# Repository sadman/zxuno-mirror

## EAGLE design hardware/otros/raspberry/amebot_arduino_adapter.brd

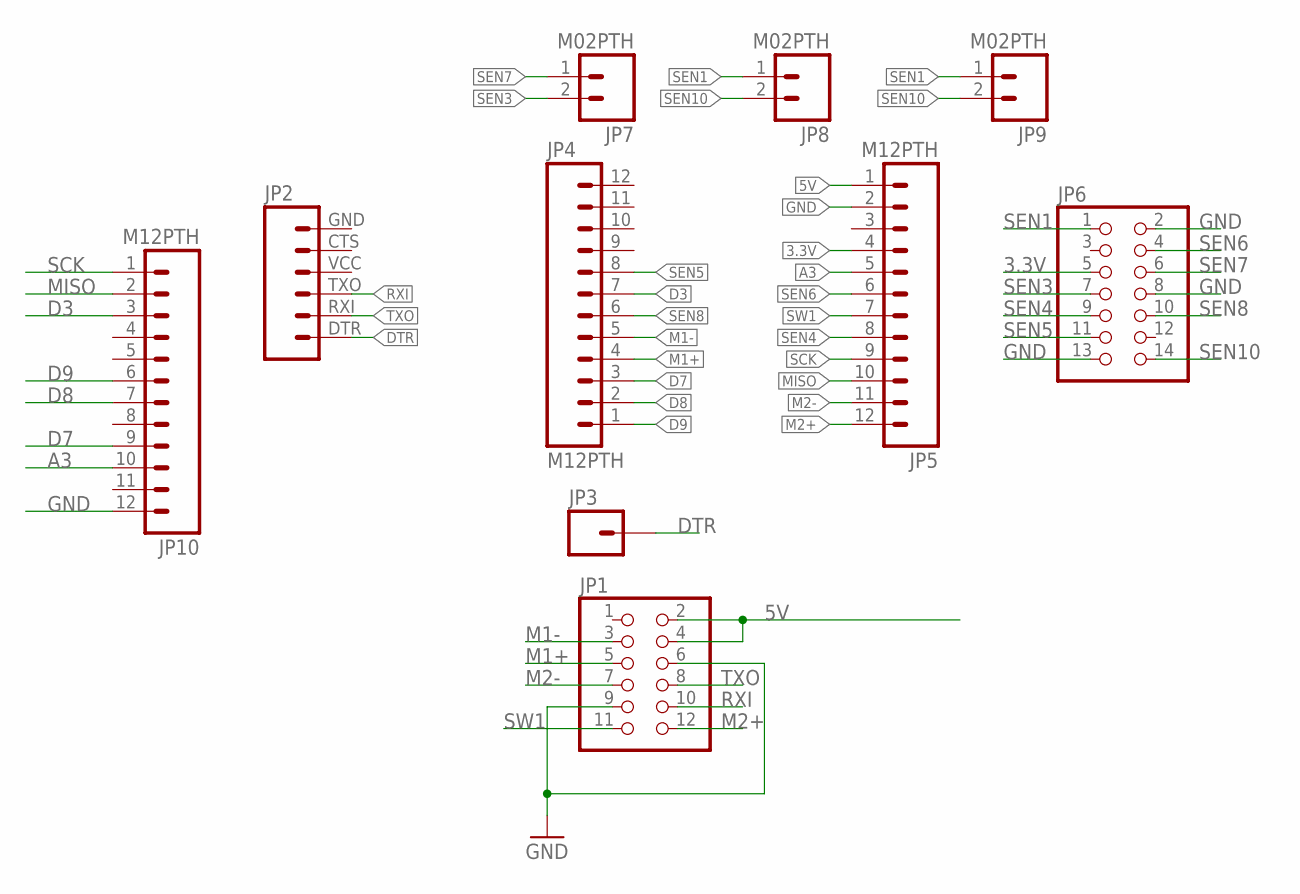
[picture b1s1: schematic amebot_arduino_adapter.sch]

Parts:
JP1: PINHD-2X6; 2X06
JP2: M06SIP; 1X06
JP3: M01PTH_LONGPAD; 1X01_LONGPAD
JP4, JP5, JP10: M12PTH; 1X12
JP6: PINHD-2X7; 2X07
JP7, JP8, JP9: M02PTH; 1X02

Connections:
3.3V: JP5.4, JP6.5
5V: JP1.2, JP1.4, JP5.1
A3: JP5.5, JP10.10
D3: JP4.7, JP10.3
D7: JP4.3, JP10.9
D8: JP4.2, JP10.7
D9: JP4.1, JP10.6
DTR: JP2.DTR (1), JP3.1
GND: JP1.6, JP1.9, JP5.2, JP6.2, JP6.8, JP6.13, JP10.12
M1+: JP1.5, JP4.4
M1-: JP1.3, JP4.5
M2+: JP1.12, JP5.12
M2-: JP1.7, JP5.11
MISO: JP5.10, JP10.2
RXI: JP1.10, JP2.TXO (3)
SCK: JP5.9, JP10.1
SEN1: JP6.1, JP8.1, JP9.1
SEN3: JP6.7, JP7.2
SEN4: JP5.8, JP6.9
SEN5: JP4.8, JP6.11
SEN6: JP5.6, JP6.4
SEN7: JP6.6, JP7.1
SEN8: JP4.6, JP6.10
SEN10: JP6.14, JP8.2, JP9.2
SW1: JP1.11, JP5.7
TXO: JP1.8, JP2.RXI (2)

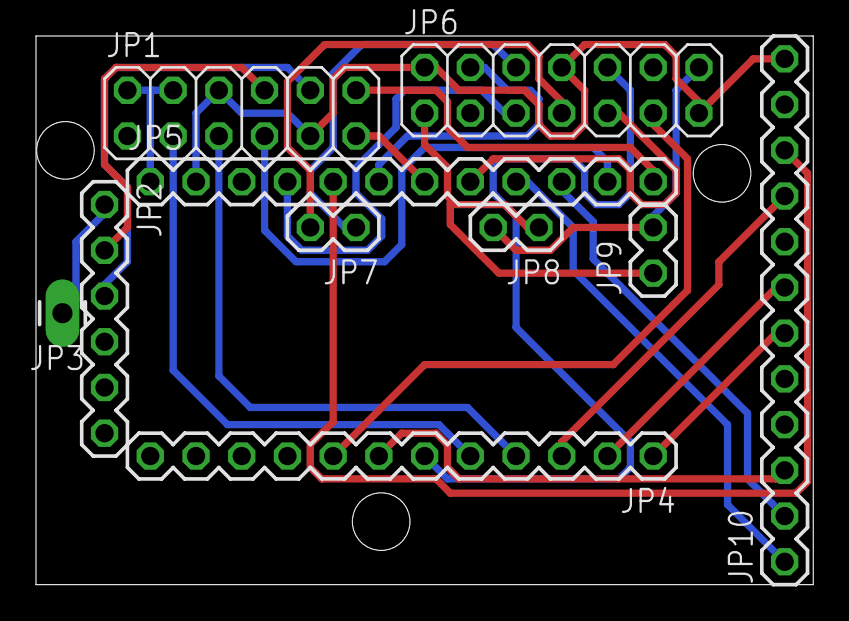
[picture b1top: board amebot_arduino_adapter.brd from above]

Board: 2 copper layers, 43.2 x 30.5 mm, 10 parts (0 on the bottom side), 26 nets.

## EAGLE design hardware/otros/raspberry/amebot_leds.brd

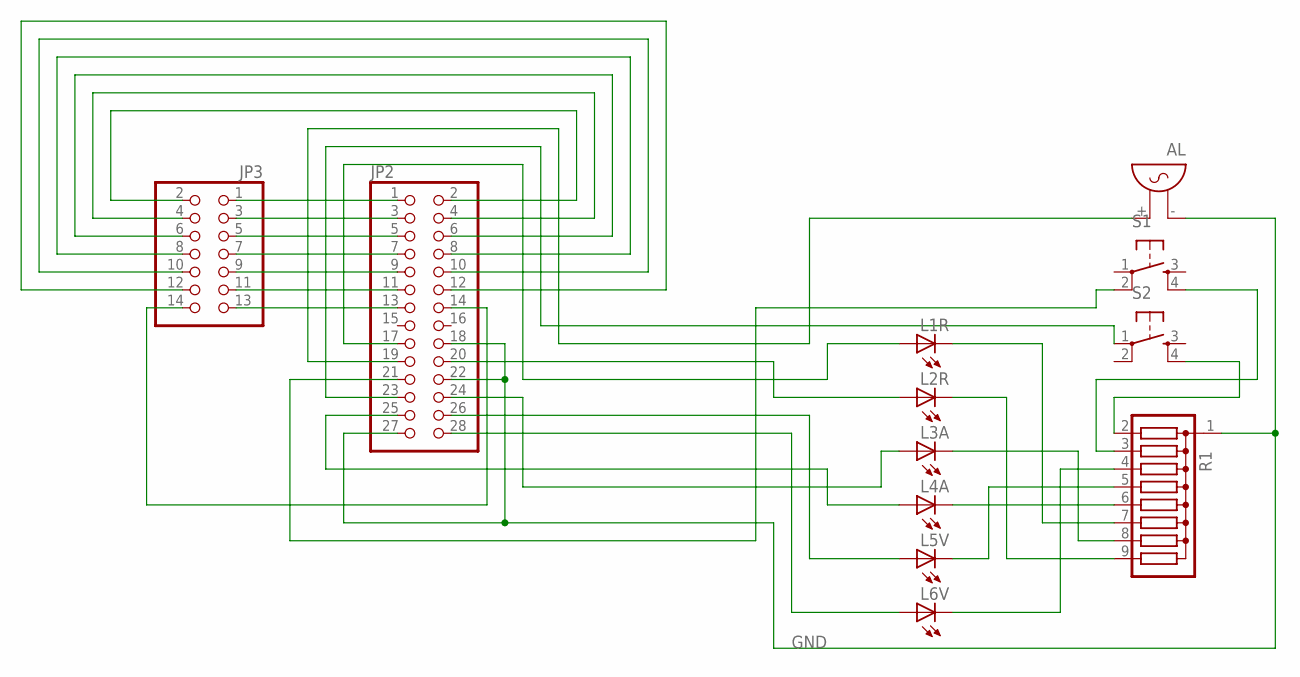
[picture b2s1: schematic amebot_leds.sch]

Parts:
AL: F/QMX
JP2: PINHD-2X14; 2X14
JP3: PINHD-2X7; 2X07
L1R, L2R, L3A, L4A, L5V, L6V: LED5MM
R1: G08R; SIL9
S1, S2: DTS-6

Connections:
GND: AL.- (1), JP2.18, JP2.22, JP2.27
unnamed: L5V.K (C), R1.5
unnamed: JP2.17, L1R.A
unnamed: L3A.K (C), R1.8
unnamed: JP2.23, S2.1
unnamed: JP2.25, L4A.A
unnamed: L4A.K (C), R1.6
unnamed: L2R.K (C), R1.9
unnamed: JP2.20, L2R.A
unnamed: L1R.K (C), R1.7
unnamed: AL.+ (2), JP2.19
unnamed: L6V.K (C), R1.4
unnamed: JP2.21, S1.2
unnamed: R1.2, S2.4
unnamed: R1.3, S1.4
unnamed: JP2.24, L3A.A
unnamed: JP2.28, L6V.A
unnamed: JP2.26, L5V.A
unnamed: JP2.1, JP3.1
unnamed: JP2.3, JP3.3
unnamed: JP2.5, JP3.5
unnamed: JP2.7, JP3.7
unnamed: JP2.9, JP3.9
unnamed: JP2.11, JP3.11
unnamed: JP2.13, JP3.13
unnamed: JP2.2, JP3.2
unnamed: JP2.4, JP3.4
unnamed: JP2.6, JP3.6
unnamed: JP2.8, JP3.8
unnamed: JP2.10, JP3.10
unnamed: JP2.12, JP3.12
unnamed: JP2.14, JP3.14

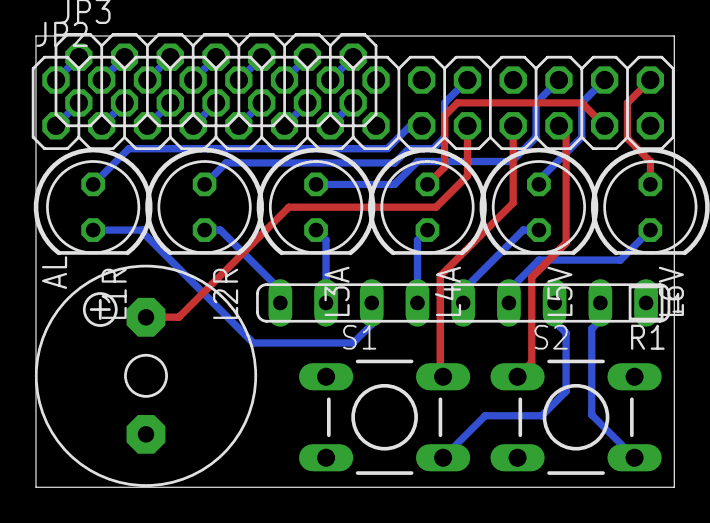
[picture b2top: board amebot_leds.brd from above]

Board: 2 copper layers, 35.5 x 25.1 mm, 12 parts (0 on the bottom side), 32 nets.

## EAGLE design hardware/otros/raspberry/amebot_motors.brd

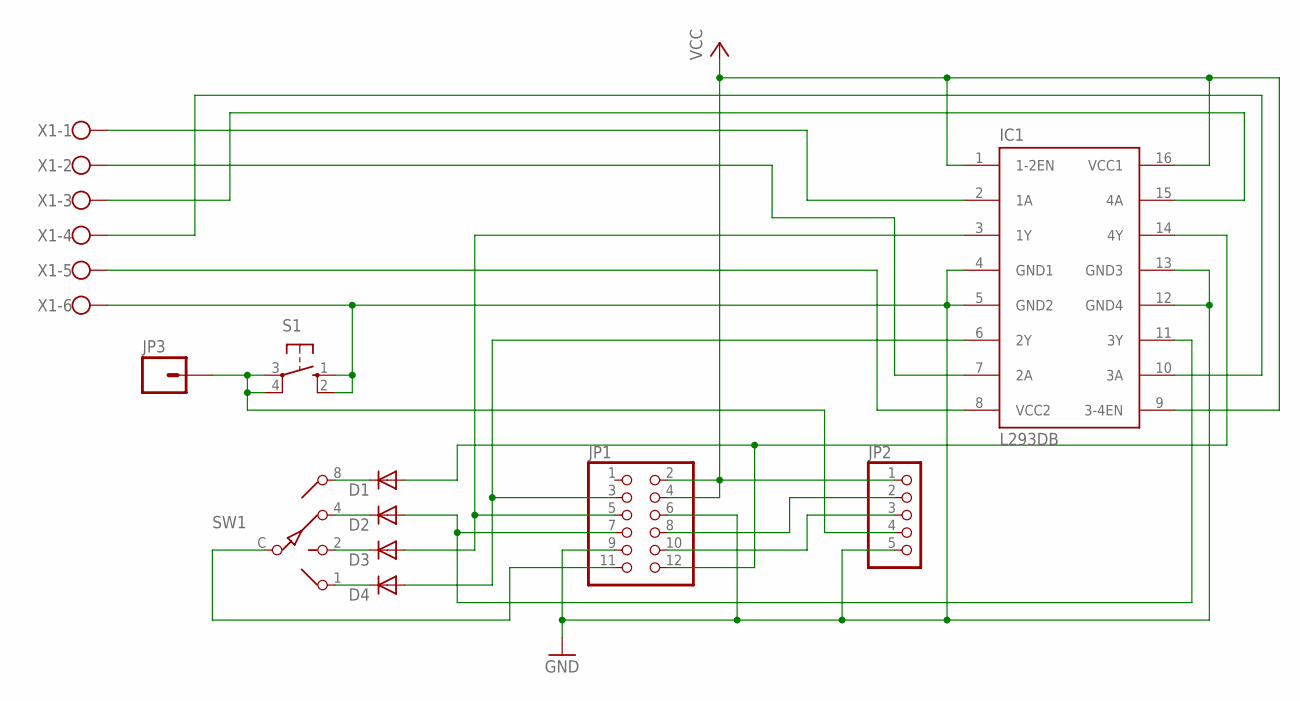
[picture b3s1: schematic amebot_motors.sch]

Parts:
D1, D2, D3, D4: DIODE-MICROMELF-W; MICROMELF-W
IC1: L293DB; DIL16VAR
JP1: PINHD-2X6; 2X06
JP2: PINHD-1X5; 1X05
JP3: M01PTH_LONGPAD; 1X01_LONGPAD
S1: 10-XX; B3F-10XX
SW1: SW-C10
X1: W237-6

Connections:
GND: IC1.4 (GND1), IC1.5 (GND2), IC1.12 (GND4), IC1.13 (GND3), JP1.6, JP1.9, JP2.5, S1.1 (S), S1.2 (S1), X1.6
unnamed: D1.C, SW1.8
unnamed: JP2.4, JP3.1, S1.3, S1.4 (P1)
unnamed: D4.A, IC1.6 (2Y), JP1.3
unnamed: D3.A, IC1.3 (1Y), JP1.5
unnamed: JP1.11, SW1.C
unnamed: D1.A, IC1.14 (4Y), JP1.12
unnamed: JP1.8, JP2.2
unnamed: IC1.2 (1A), X1.1
unnamed: IC1.7 (2A), X1.2
unnamed: IC1.15 (4A), X1.3
unnamed: IC1.10 (3A), X1.4
unnamed: IC1.8 (VCC2), X1.5
unnamed: JP1.10, JP2.3
unnamed: D2.A, IC1.11 (3Y), JP1.7
unnamed: D2.C, SW1.4
unnamed: D3.C, SW1.2
unnamed: D4.C, SW1.1
VCC: IC1.1 (1-2EN), IC1.9 (3-4EN), IC1.16 (VCC1), JP1.2, JP1.4, JP2.1

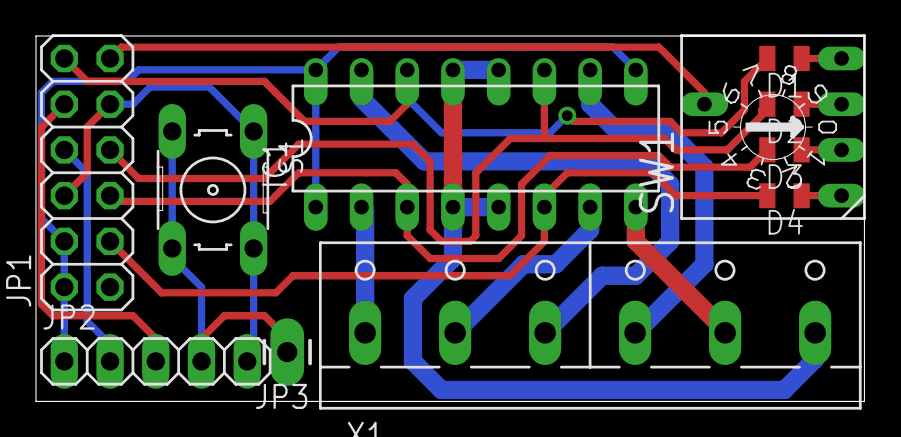
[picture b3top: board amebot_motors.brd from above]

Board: 2 copper layers, 46.0 x 20.3 mm, 11 parts (0 on the bottom side), 19 nets.

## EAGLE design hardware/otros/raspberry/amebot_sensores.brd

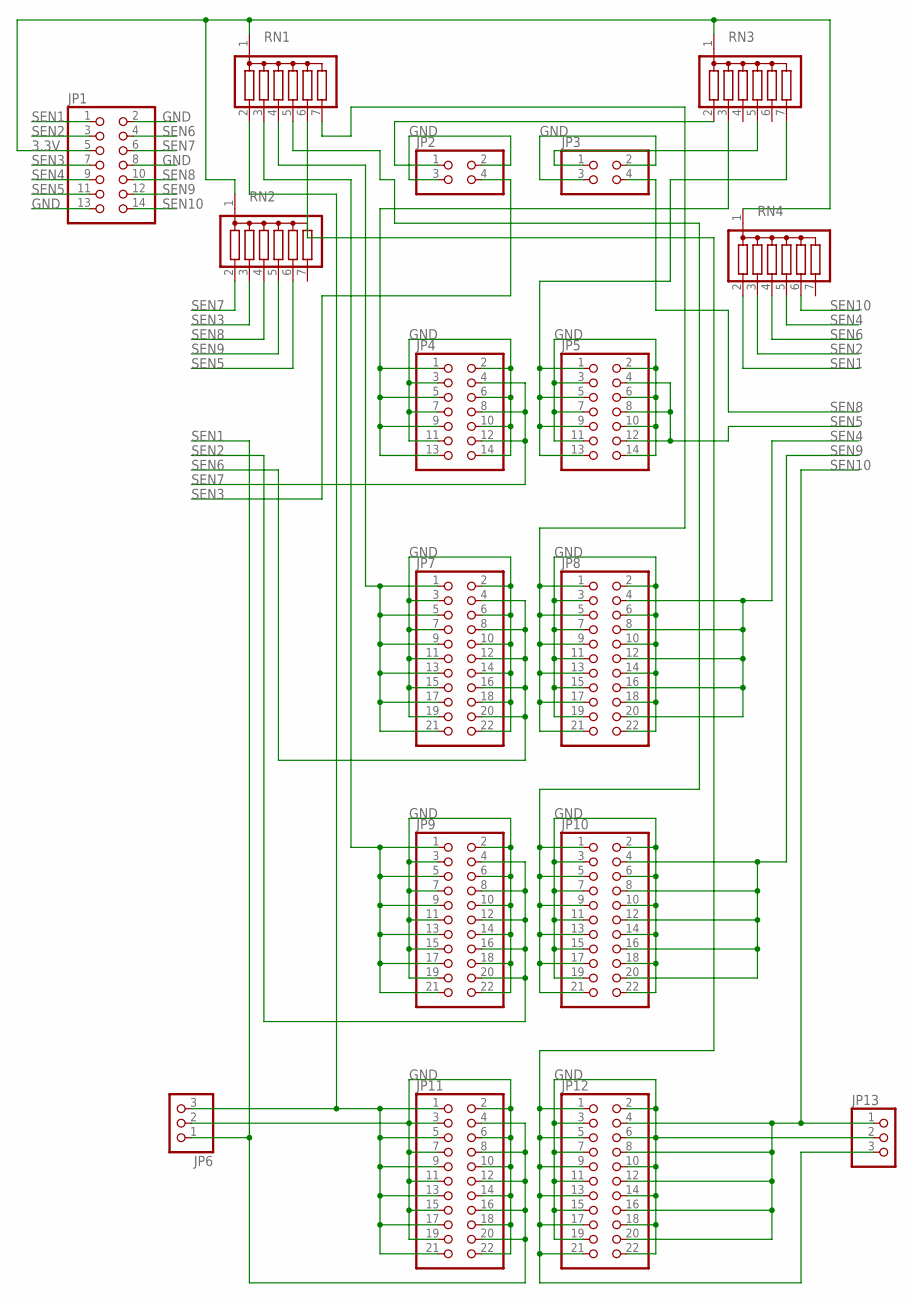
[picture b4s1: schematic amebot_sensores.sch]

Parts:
JP1, JP4, JP5: PINHD-2X7; 2X07
JP2, JP3: PINHD-2X2; 2X02
JP6, JP13: PINHD-1X3; 1X03
JP7, JP8, JP9, JP10, JP11, JP12: PINHD-2X11; 2X11
RN1, RN2, RN3, RN4: G06R; SIL7

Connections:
3.3V: JP1.5, RN1.1, RN2.1, RN3.1, RN4.1
GND: JP1.2, JP1.8, JP1.13, JP2.2, JP2.3, JP3.2, JP3.3, JP4.2, JP4.3, JP4.6, JP4.7, JP4.10, JP4.11, JP4.14, JP5.2, JP5.3, JP5.6, JP5.7, JP5.10, JP5.11, JP5.14, JP6.2, JP7.2, JP7.3, JP7.6, JP7.7, JP7.10, JP7.11, JP7.14, JP7.15, JP7.18, JP7.19, JP7.22, JP8.2, JP8.3, JP8.6, JP8.7, JP8.10, JP8.11, JP8.14, JP8.15, JP8.18, JP8.19, JP8.22, JP9.2, JP9.3, JP9.6, JP9.7, JP9.10, JP9.11, JP9.14, JP9.15, JP9.18, JP9.19, JP9.22, JP10.2, JP10.3, JP10.6, JP10.7, JP10.10, JP10.11, JP10.14, JP10.15, JP10.18, JP10.19, JP10.22, JP11.2, JP11.3, JP11.6, JP11.7, JP11.10, JP11.11, JP11.14, JP11.15, JP11.18, JP11.19, JP11.22, JP12.2, JP12.3, JP12.6, JP12.7, JP12.10, JP12.11, JP12.14, JP12.15, JP12.18, JP12.19, JP12.22, JP13.2
unnamed: JP8.1, JP8.5, JP8.9, JP8.13, JP8.17, JP8.21, RN1.7
unnamed: JP2.1, RN3.2
unnamed: JP7.1, JP7.5, JP7.9, JP7.13, JP7.17, JP7.21, RN1.4
unnamed: JP4.1, JP4.5, JP4.9, JP4.13, RN3.3
unnamed: JP5.1, JP5.5, JP5.9, JP5.13, RN3.7
unnamed: JP3.1, RN3.5
unnamed: JP12.1, JP12.5, JP12.9, JP12.13, JP12.17, JP12.21, JP13.3, RN1.6
unnamed: JP6.3, JP11.1, JP11.5, JP11.9, JP11.13, JP11.17, JP11.21, RN1.2
unnamed: JP9.1, JP9.5, JP9.9, JP9.13, JP9.17, JP9.21, RN1.3
unnamed: JP10.1, JP10.5, JP10.9, JP10.13, JP10.17, JP10.21, RN1.5
SEN1: JP1.1, JP6.1, JP11.4, JP11.8, JP11.12, JP11.16, JP11.20, RN4.2
SEN2: JP1.3, JP9.4, JP9.8, JP9.12, JP9.16, JP9.20, RN4.3
SEN3: JP1.7, JP2.4, RN2.3
SEN4: JP1.9, JP8.4, JP8.8, JP8.12, JP8.16, JP8.20, RN4.5
SEN5: JP1.11, JP5.4, JP5.8, JP5.12, RN2.6
SEN6: JP1.4, JP7.4, JP7.8, JP7.12, JP7.16, JP7.20, RN4.4
SEN7: JP1.6, JP4.4, JP4.8, JP4.12, RN2.2
SEN8: JP1.10, JP3.4, RN2.4
SEN9: JP1.12, JP10.4, JP10.8, JP10.12, JP10.16, JP10.20, RN2.5
SEN10: JP1.14, JP12.4, JP12.8, JP12.12, JP12.16, JP12.20, JP13.1, RN4.6

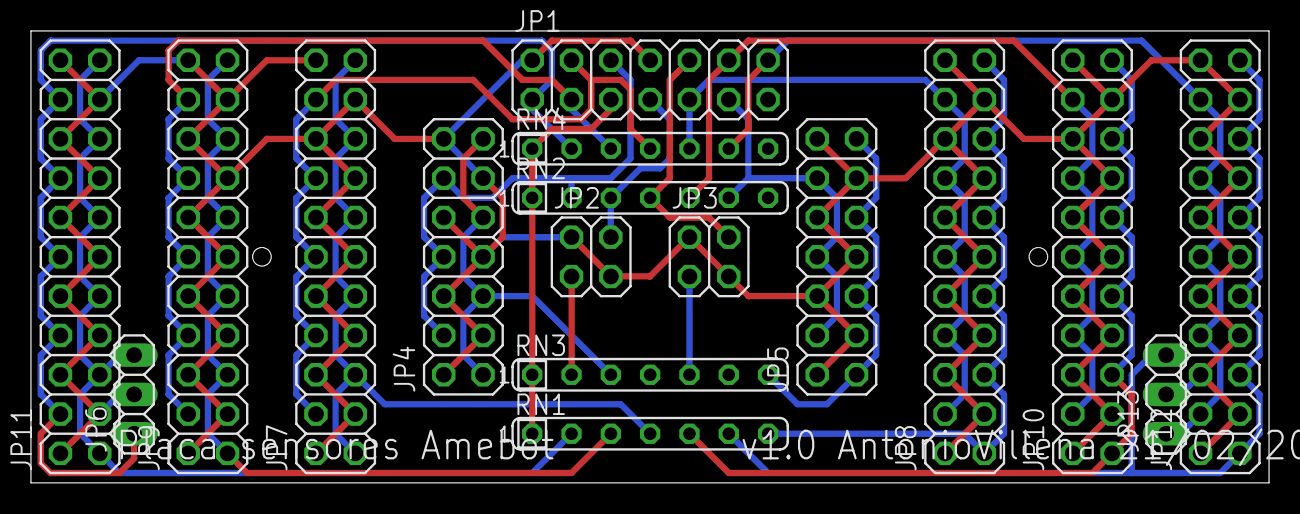
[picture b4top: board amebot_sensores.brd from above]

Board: 2 copper layers, 80.0 x 29.2 mm, 17 parts (0 on the bottom side), 22 nets.

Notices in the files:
parts and their libraries:
SparkFun-Connectors: Licensing: Creative Commons ShareAlike 4.0 International - https://creativecommons.org/licenses/by-sa/4.0
